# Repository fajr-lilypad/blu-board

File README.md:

# blu-board

Blu-Board is a custom devboard (my first!) Built off of a RP2040, this is a more advanced project so I could get used to complex routing, placement, and assembly. I started this off using a guide, which I consulted for fabrication, materials, and for when I ran into DRC errors I'm not familair with. I decided to customize it and add a special LED that will glow periodically. I made it with the intention of creating a PCB that would be my most diificult to route yet in order to challenge myself, and it definetly was! I had a goal of creating a clean and compact pcb design, one that is minimalist and just allows you to have direct access to the RP2040, and will fit into tight spaces! Breadboard friendly and with an LED for code-tetsting, this is a friendly board to use with my beginner projects, with an LED for simple debugging and testing :)

## PCB Layout 

This took a lot of time, but was worth it in the end! It taught me a lot about routing, thermal reliefs, and mindful placement. It was my first time working with a flash memory card or a crystal oscillator in a pcb, too!
<table>
  <tr>
    <td>
      
    </td>
    <td>
    
    </td>
  </tr>
</table>

## Schematic Wiring Diagram

## Zine

## BOM
| Item | Qty | Purpose | Price | Source | Link |
| :--- | :---: | :--- | :---: | :--- | :--- |
| Raspberry Pi RP2040 | 1 | Microcontroller | $0.80 | PiShopUSA | [Link](https://www.pishop.us/product/raspberry-pi-rp2040/?srsltid=AfmBOorSiPwZ4N7HXN2U0b0knYWJnlClnwnstZDdNLLsMam4UAugIxdB4rs) |
| 1x20 Pin Header | 2 | Pins | $1.34 | Mikroe | [Link](https://www.mikroe.com/1x20-male-pin-header?srsltid=AfmBOopXewJdVJScYL7vcy0ZBhXL1PcT3TNst3e0l6S0080vmtMOhk3b-Mc) |
| 0.1uF C | 12 | Capacitor | $3.84 | Sparkfun | [Link](https://www.sparkfun.com/capacitor-ceramic-0-1uf.html) |
| 5.1k R | 2 | Resistor | $0.08 | Electronix Express | [Link](https://www.elexp.com/products/130155-1kres-1-watt-5-5-1-k-ohm?variant=42620564504804&country=US&currency=USD&utm_medium=product_sync&utm_source=google&utm_content=sag_organic&utm_campaign=sag_organic&srsltid=AfmBOoqKgWPBG0shD9zpuYg7Psf4nfMv1r5sR8Nr0Ir3SL3qnrRQrXJ_9UA) |
| 10uF C | 2 | Capacitor | $0.40 | DigiKey | [Link](https://www.digikey.com/en/products/detail/kyocera-avx/REA0511100M025K/20096372?gclsrc=aw.ds&gad_source=1&gad_campaignid=20682862038&gbraid=0AAAAADrbLlg0zCO2nMN9oOFXGoIwVJrS6&gclid=Cj0KCQjw0JnRBhDJARIsALobnXYPCey9XhELbus8p4oBeSzUM1fkyno59aOY1zw6VVWGtJGkAox3TrsaAmw4EALw_wcB) |
| 1K R | 2 | Resistor | $0.20 | DigiKey | [Link](https://www.digikey.com/en/products/detail/yageo/MFR-25FTF52-1K/9140604?gclsrc=aw.ds&gad_source=1&gad_campaignid=17335707486&gbraid=0AAAAADrbLlgqnE17MBySLl412xT3dFUeL&gclid=Cj0KCQjw0JnRBhDJARIsALobnXakpvVYdOGztgsvtSKwE79AdJEvhnWEkEIyQ3gdhkyJx4jX317zDJkaAjerEALw_wcB) |
| 1x03 Pin Header | 1 | Pins | $0.23 | Mouser Electronics | [Link](https://www.mouser.com/ProductDetail/Harwin/M22-2510305?qs=Z7IUn5gUMVONkEjocUd7kg%3D%3D&mgh=1&utm_id=22288723604&utm_source=google&utm_medium=cpc&utm_marketing_tactic=amercorp&gad_source=4&gad_campaignid=22288726694&gbraid=0AAAAADn_wf30N259TnrufS_TZFJDTtaHg&gclid=Cj0KCQjw0JnRBhDJARIsALobnXZQLsWtaPO5afch1NSt4Pu2yZkarmpP5d_HRQKpA2yGJk3OKvz3ylQaAmbOEALw_wcB) |
| 1uF C | 2 | Capacitor | $0.40 | DigiKey | [Link](https://www.digikey.com/en/products/detail/kyocera-avx/REA05111R0M050K/20096513?gclsrc=aw.ds&gad_source=1&gad_campaignid=20682862038&gbraid=0AAAAADrbLlg0zCO2nMN9oOFXGoIwVJrS6&gclid=Cj0KCQjw0JnRBhDJARIsALobnXbjebcoAmcIRErazcBxw3UNkIyXNPoxNc7ANFcH5uaAV1FzOTPnl4QaArwpEALw_wcB) |
| 33pf C | 2 | Capacitor | $1.12 | DigiKey | [Link](https://www.digikey.com/en/products/detail/murata-electronics/RCE5C2A330J0M1H03A/4277083?gclsrc=aw.ds&gad_source=1&gad_campaignid=20509818233&gbraid=0AAAAADrbLlied6U1PO-X9vgylrs8pLi1n&gclid=Cj0KCQjw0JnRBhDJARIsALobnXZYgGnIDuHKfOUllKuRLUyinVjaLLaJfXFdjW9Wg1789fI8Et_OJPEaAqfQEALw_wcB) |
| WS2812B | 1 | LED | $0.10 | Ebee | [Link](https://www.ebee.com/product-detail/worldsemi-ws2812b-v5-w_617514.html?gad_source=1&gad_campaignid=22818797232&gbraid=0AAAABAZS-mZ97kvrRYudRCfHYeKSVd23P&gclid=Cj0KCQjw0JnRBhDJARIsALobnXbpNoaM8TbHHZTgba2UspdfY-oN8lfFjU0dsez_f3c1VV_Ib0_YNKMaAifpEALw_wcB) |
| MCP1700x-330xxTT | 1 | Regulator | $0.51 | DigiKey | [Link](https://www.digikey.com/en/products/detail/microchip-technology/MCP1700T-3302E-TT/652676?msockid=2e5d5b722df0614517334d312c7660e6) |
| USB C Receptacle | 1 | Connector | $0.91 | DigiKey | [Link](https://www.digikey.com/en/products/detail/gct/USB4085-GF-A/9859662?msockid=2e5d5b722df0614517334d312c7660e6) |
| 12 MHz Crystal SMD | 1 | Crystal | $0.50 | Mouser Electronics | [Link](https://www.mouser.com/ProductDetail/Wurth-Elektronik/830105420809?qs=hd1VzrDQEGhFJmLFyoYByw%3D%3D) |
| 330 Ohm Chip R | 1 | Resistor | $0.10 | DigiKey | [Link](https://www.digikey.com/en/products/detail/yageo/RT0402FRE07330RL/1071958) |
| W25Q128JVS | 1 | Memory Chip | $1.87 | Buy Display | [Link](https://www.buydisplay.com/new-winbond-ic-chip-flash-128m-bit-w25q128jv-sop8-package?srsltid=AfmBOorTtHa9eSnclcz9y9MKXpbE52O-UkMt6bnDD7wcOpvxAkhcAFfxirI) |
| 27K R | 2 | Resistor | $0.42 | Newark | [Link](https://www.newark.com/multicomp-pro/mf25-27k/res-27k-250mw-axial-metal-film/dp/38K5324?cjdata=MXxOfDB8WXww&CMP=AFF-CJ-101375778-Newark+Redirect+Link&gad_source=1&gad_campaignid=22957739450&gbraid=0AAAAAD5U_g2ATgQ2NG2je9ALfN8sx9jn8&gclid=Cj0KCQjw0JnRBhDJARIsALobnXZpBhV4gM6cjgULH4YQ3_HOMMbNESm9YJqxlcUMUdGeT429-VJUSysaArluEALw_wcB&source=CJ&cjevent=34edd5a2637611f181a1063b0a82b82a&loyaltysignal=0) |
| 10K R | 1 | Resistor | $0.19 | Newark | [Link](https://www.newark.com/multicomp-pro/mf12-10k/res-10k-125mw-axial-metal-film/dp/38K5401?CMP=KNC-GUSA-PMAX-SHOPPING-ONBOARD-COMP-NEW&gad_source=1&gad_campaignid=22957739450&gbraid=0AAAAAD5U_g2ATgQ2NG2je9ALfN8sx9jn8&gclid=Cj0KCQjw0JnRBhDJARIsALobnXaCMZy09SS6FHr-OHNYzwHpClJ-m80lx3xV-T8LpQe5MepvkQgdvkEaAqznEALw_wcB) |
| SW Push | 1 | Button | $0.11 | SameSky | [Link](https://www.sameskydevices.com/product/switches/tactile-switches/ts02-66-60-bk-260-lcr-d?gad_source=1&gad_campaignid=21298951355&gbraid=0AAAAACohXz1fiXhj2T0FMprjXrLrWC8G8&gclid=Cj0KCQjw0JnRBhDJARIsALobnXa_TaIyqQXn2UFvrIDqeu8W0gxQuIBMibr_Leqg33zKeuVPJBAM3IcaAuDZEALw_wcB) |
| PCB Order | 1 | PCB | $2.10 | JLCPCB | [Link](https://cart.jlcpcb.com/quote?stencilLayer=2&stencilWidth=100&stencilLength=100&stencilCounts=5&plateType=1&spm=Jlcpcb.Homepage.1010) |
| **Subtotal** | | | **$15.22** | | |

## Notes and Acknoweldgements
Thank you to the hackclub and fallout team for making this possible!

Thank you user KaiPereira for a super helpful guide on devboards and all things PCB! I learned so much!

"Blu - Board" font courtesy of Alit Design Studio

All artwork belongs to respective creators.

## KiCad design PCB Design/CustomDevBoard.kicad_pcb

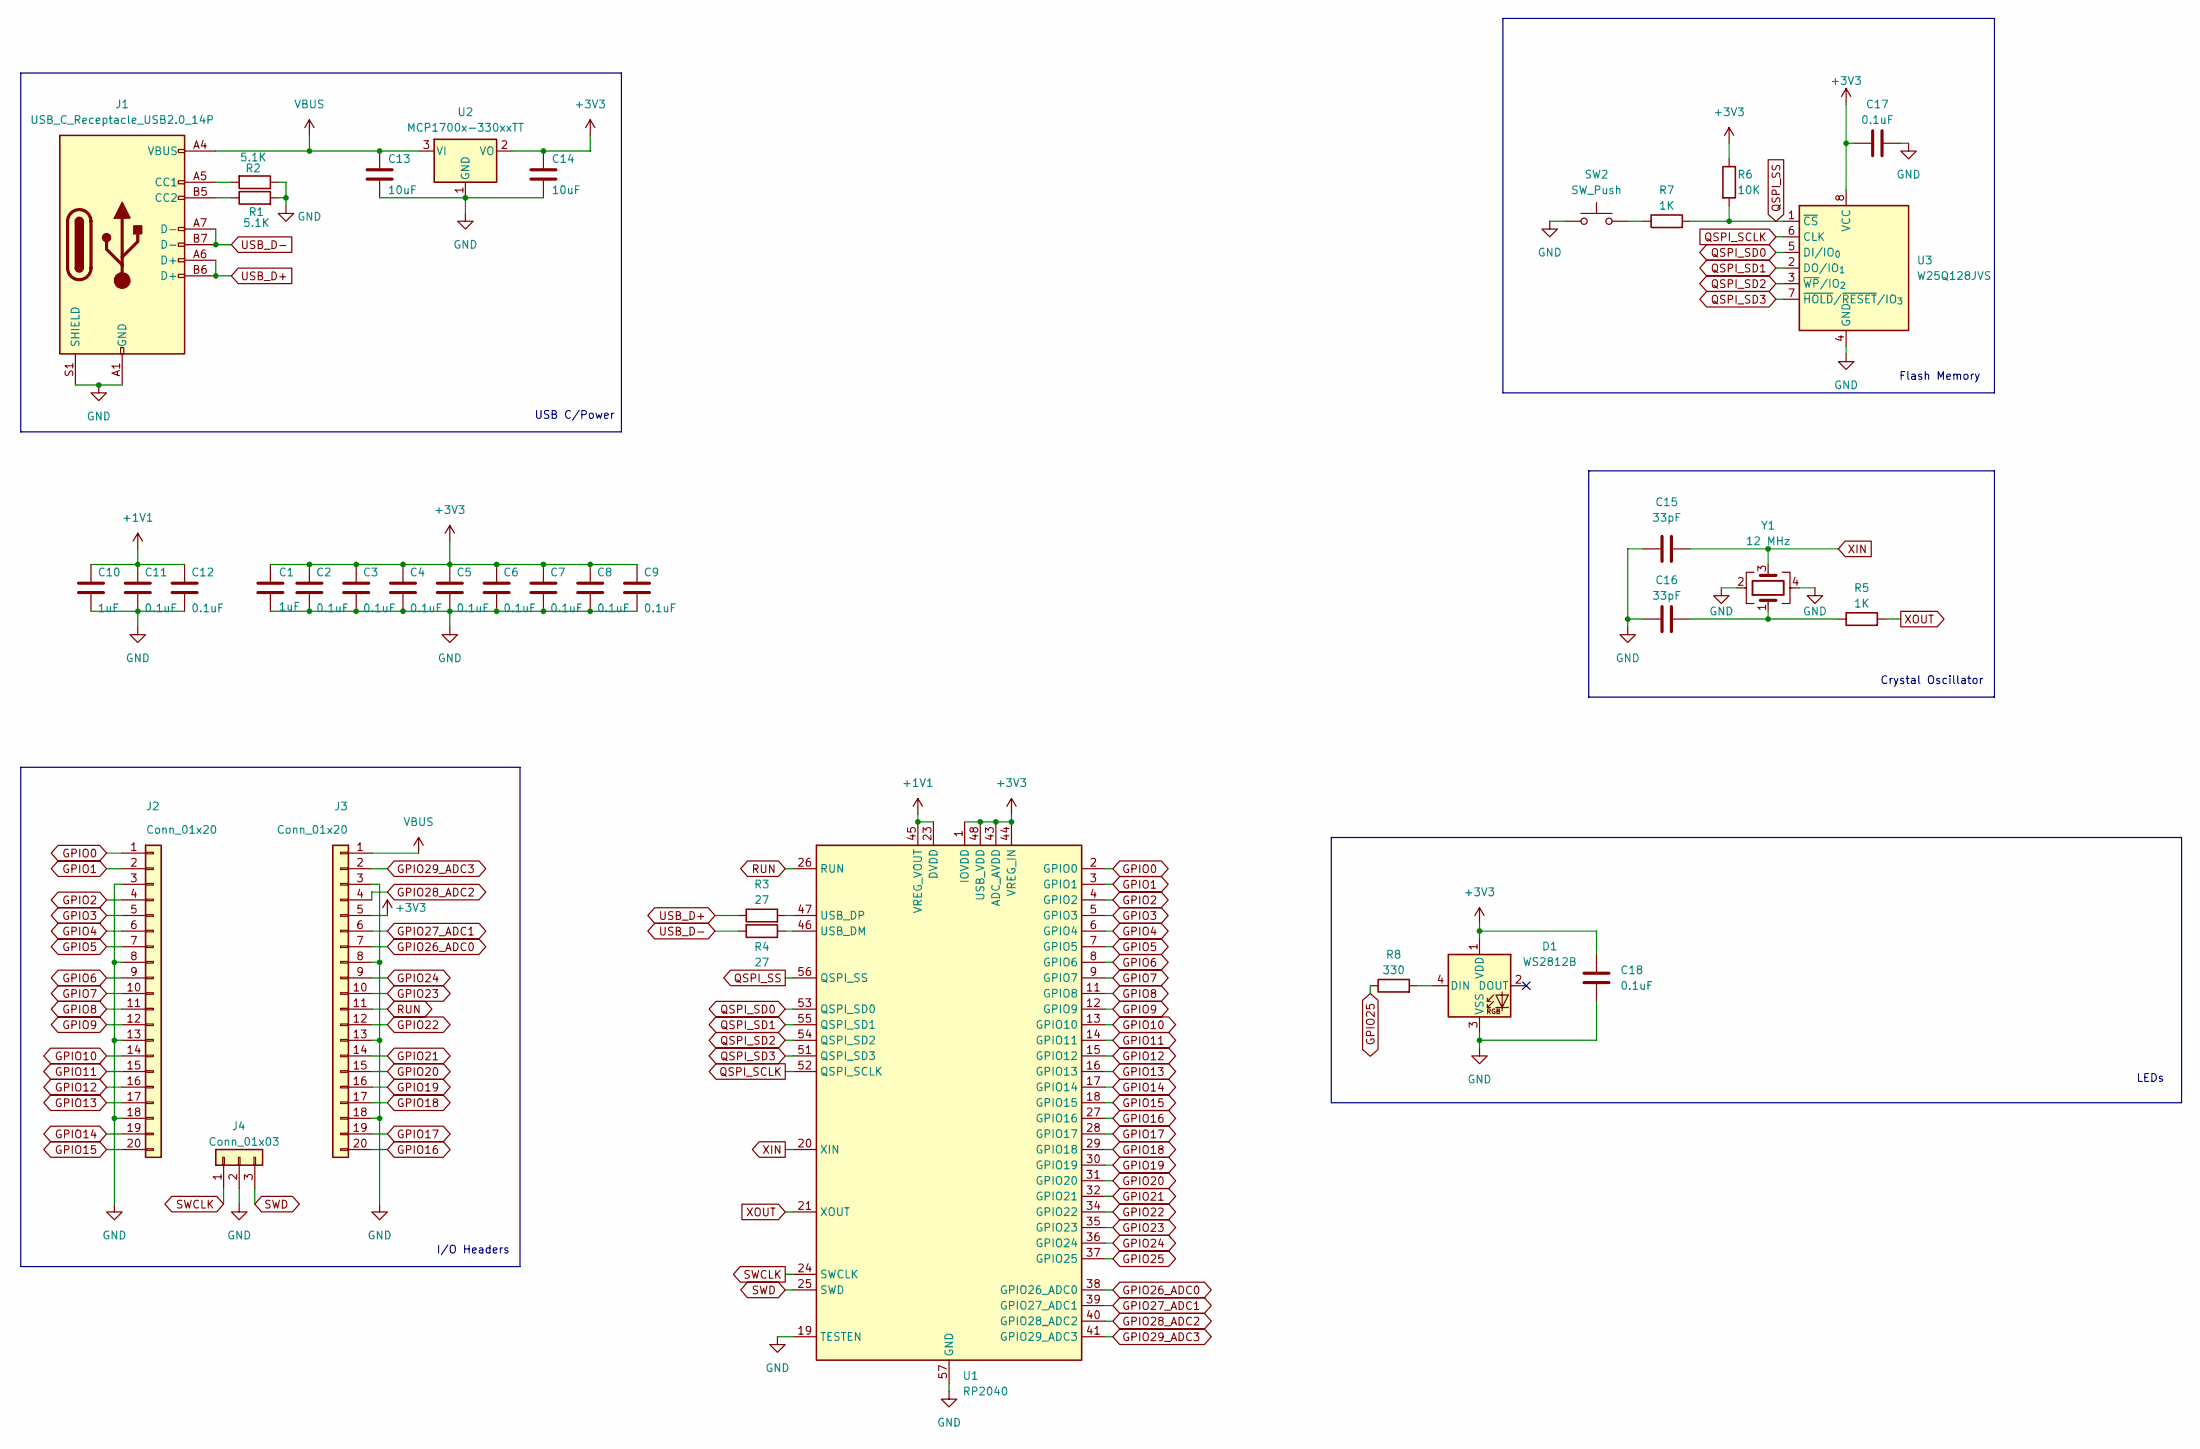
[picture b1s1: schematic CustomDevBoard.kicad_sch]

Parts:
C1, C10: 1uF; C_0402_1005Metric
C2, C3, C4, C5, C6, C7, C8, C9, C11, C12, C17, C18: 0.1uF; C_0402_1005Metric
C13, C14: 10uF; C_0201_0603Metric
C15, C16: 33pF; C_0402_1005Metric
D1: WS2812B; LED_WS2812B_PLCC4_5.0x5.0mm_P3.2mm
J1: USB_C_Receptacle_USB2.0_14P; USB_C_Receptacle_HRO_TYPE-C-31-M-12
J2, J3: Conn_01x20; PinHeader_1x20_P2.54mm_Vertical
J4: Conn_01x03; PinHeader_1x03_P2.54mm_Vertical
R1, R2: 5.1K; R_0402_1005Metric
R3, R4: 27; R_0402_1005Metric
R5, R7: 1K; R_0402_1005Metric
R6: 10K; R_0402_1005Metric
R8: 330; R_0402_1005Metric
SW2: SW_Push; SW_Push_SPST_NO_Alps_SKRK
U1: RP2040; QFN-56-1EP_7x7mm_P0.4mm_EP3.2x3.2mm
U2: MCP1700x-330xxTT; SOT-23
U3: W25Q128JVS; Winbond_USON-8-1EP_3x2mm_P0.5mm_EP0.2x1.6mm
Y1: 12 MHz; Crystal_SMD_3225-4Pin_3.2x2.5mm

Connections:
+1V1: C10.1, C11.1, C12.1, U1.23 (DVDD), U1.45 (VREG_VOUT), U1.50 (DVDD)
+3V3: C1.1, C2.1, C3.1, C4.1, C5.1, C6.1, C7.1, C8.1, C9.1, C14.1, C17.1, C18.1, D1.1 (VDD), J3.5, R6.1, U1.1 (IOVDD), U1.10 (IOVDD), U1.22 (IOVDD), U1.33 (IOVDD), U1.42 (IOVDD), U1.43 (ADC_AVDD), U1.44 (VREG_IN), U1.48 (USB_VDD), U1.49 (IOVDD), U2.2 (VO), U3.8 (VCC)
GND: C1.2, C2.2, C3.2, C4.2, C5.2, C6.2, C7.2, C8.2, C9.2, C10.2, C11.2, C12.2, C13.2, C14.2, C15.1, C16.2, C17.2, C18.2, D1.3 (VSS), J1.A1 (GND), J1.A12 (GND), J1.B1 (GND), J1.B12 (GND), J1.S1 (SHIELD), J2.3, J2.8, J2.13, J2.18, J3.3, J3.8, J3.13, J3.18, J4.2, R1.2, R2.1, SW2.1, U1.19 (TESTEN), U1.57 (GND), U2.1 (GND), U3.4 (GND), Y1.2, Y1.4
GPIO0: J2.1, U1.2 (GPIO0)
GPIO1: J2.2, U1.3 (GPIO1)
GPIO2: J2.4, U1.4 (GPIO2)
GPIO3: J2.5, U1.5 (GPIO3)
GPIO4: J2.6, U1.6 (GPIO4)
GPIO5: J2.7, U1.7 (GPIO5)
GPIO6: J2.9, U1.8 (GPIO6)
GPIO7: J2.10, U1.9 (GPIO7)
GPIO8: J2.11, U1.11 (GPIO8)
GPIO9: J2.12, U1.12 (GPIO9)
GPIO10: J2.14, U1.13 (GPIO10)
GPIO11: J2.15, U1.14 (GPIO11)
GPIO12: J2.16, U1.15 (GPIO12)
GPIO13: J2.17, U1.16 (GPIO13)
GPIO14: J2.19, U1.17 (GPIO14)
GPIO15: J2.20, U1.18 (GPIO15)
GPIO16: J3.20, U1.27 (GPIO16)
GPIO17: J3.19, U1.28 (GPIO17)
GPIO18: J3.17, U1.29 (GPIO18)
GPIO19: J3.16, U1.30 (GPIO19)
GPIO20: J3.15, U1.31 (GPIO20)
GPIO21: J3.14, U1.32 (GPIO21)
GPIO22: J3.12, U1.34 (GPIO22)
GPIO23: J3.10, U1.35 (GPIO23)
GPIO24: J3.9, U1.36 (GPIO24)
GPIO25: R8.1, U1.37 (GPIO25)
GPIO26_ADC0: J3.7, U1.38 (GPIO26_ADC0)
GPIO27_ADC1: J3.6, U1.39 (GPIO27_ADC1)
GPIO28_ADC2: J3.4, U1.40 (GPIO28_ADC2)
GPIO29_ADC3: J3.2, U1.41 (GPIO29_ADC3)
unnamed: C16.1, R5.1, Y1.1
unnamed: D1.4 (DIN), R8.2
unnamed: J1.A5 (CC1), R2.2
unnamed: J1.B5 (CC2), R1.1
unnamed: R7.1, SW2.2
unnamed: R4.1, U1.46 (USB_DM)
unnamed: R3.2, U1.47 (USB_DP)
QSPI_SCLK: U1.52 (QSPI_SCLK), U3.6 (CLK)
QSPI_SD0: U1.53 (QSPI_SD0), U3.5 (DI/IO_{0})
QSPI_SD1: U1.55 (QSPI_SD1), U3.2 (DO/IO_{1})
QSPI_SD2: U1.54 (QSPI_SD2), U3.3 (~WP/IO_{2})
QSPI_SD3: U1.51 (QSPI_SD3), U3.7 (~HOLD/~RESET/IO_{3})
QSPI_SS: R6.2, R7.2, U1.56 (QSPI_SS), U3.1 (~CS)
RUN: J3.11, U1.26 (RUN)
SWCLK: J4.1, U1.24 (SWCLK)
SWD: J4.3, U1.25 (SWD)
USB_D+: J1.A6 (D+), J1.B6 (D+), R3.1
USB_D-: J1.A7 (D-), J1.B7 (D-), R4.2
VBUS: C13.1, J1.A4 (VBUS), J1.A9 (VBUS), J1.B4 (VBUS), J1.B9 (VBUS), J3.1, U2.3 (VI)
XIN: C15.2, U1.20 (XIN), Y1.3
XOUT: R5.2, U1.21 (XOUT)

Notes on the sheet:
Crystal Oscillator
I/O Headers
LEDs
USB C/Power
Flash Memory

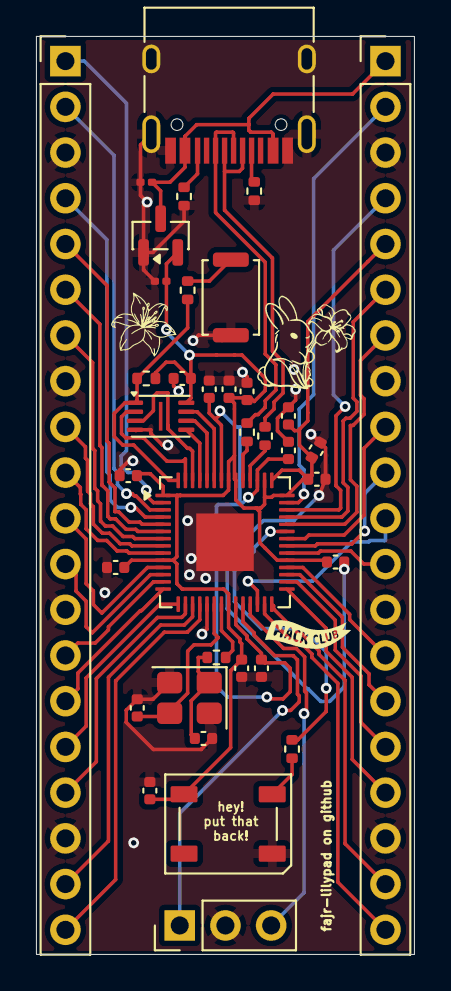
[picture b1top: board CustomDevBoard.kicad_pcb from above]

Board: 2 copper layers, 21.0 x 51.0 mm, 36 parts (0 on the bottom side), 54 nets.

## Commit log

2026-06-08 Rename CustomDevBoard.kicad_pcb to PCB Design/CustomDevBoard.kicad_pcb
2026-06-08 Rename CustomDevBoard.kicad_prl to PCB Design/ CustomDevBoard.kicad_prl
2026-06-08 Rename CustomDevBoard.kicad_pro to PCB Design/CustomDevBoard.kicad_pro
2026-06-08 Rename CustomDevBoard.kicad_sch to PCB Design/CustomDevBoard.kicad_sch
2026-06-08 Rename Screenshot 2026-06-08 145140.png to 3dViewerFront.png
2026-06-08 Rename Screenshot 2026-06-08 145201.png to 3dViewerBack.png
2026-06-08 Rename Blue Board Assembly.f3z to CAD/Blu - Board Assembly.f3z
2026-06-08 Rename Screenshot 2026-06-08 152114.png to Schematic/Schematic.png
2026-06-09 Rename Blue Board Assembly.step to Blu - Board Assembly.step
2026-06-10 Rename blu-board-zine.pdf.pdf to blu-board-zine.pdf
